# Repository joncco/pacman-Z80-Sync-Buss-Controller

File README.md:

This is a reproduction of the Z80 Sync Buss Controller used in Midway's Pac-Man arcade PCB.

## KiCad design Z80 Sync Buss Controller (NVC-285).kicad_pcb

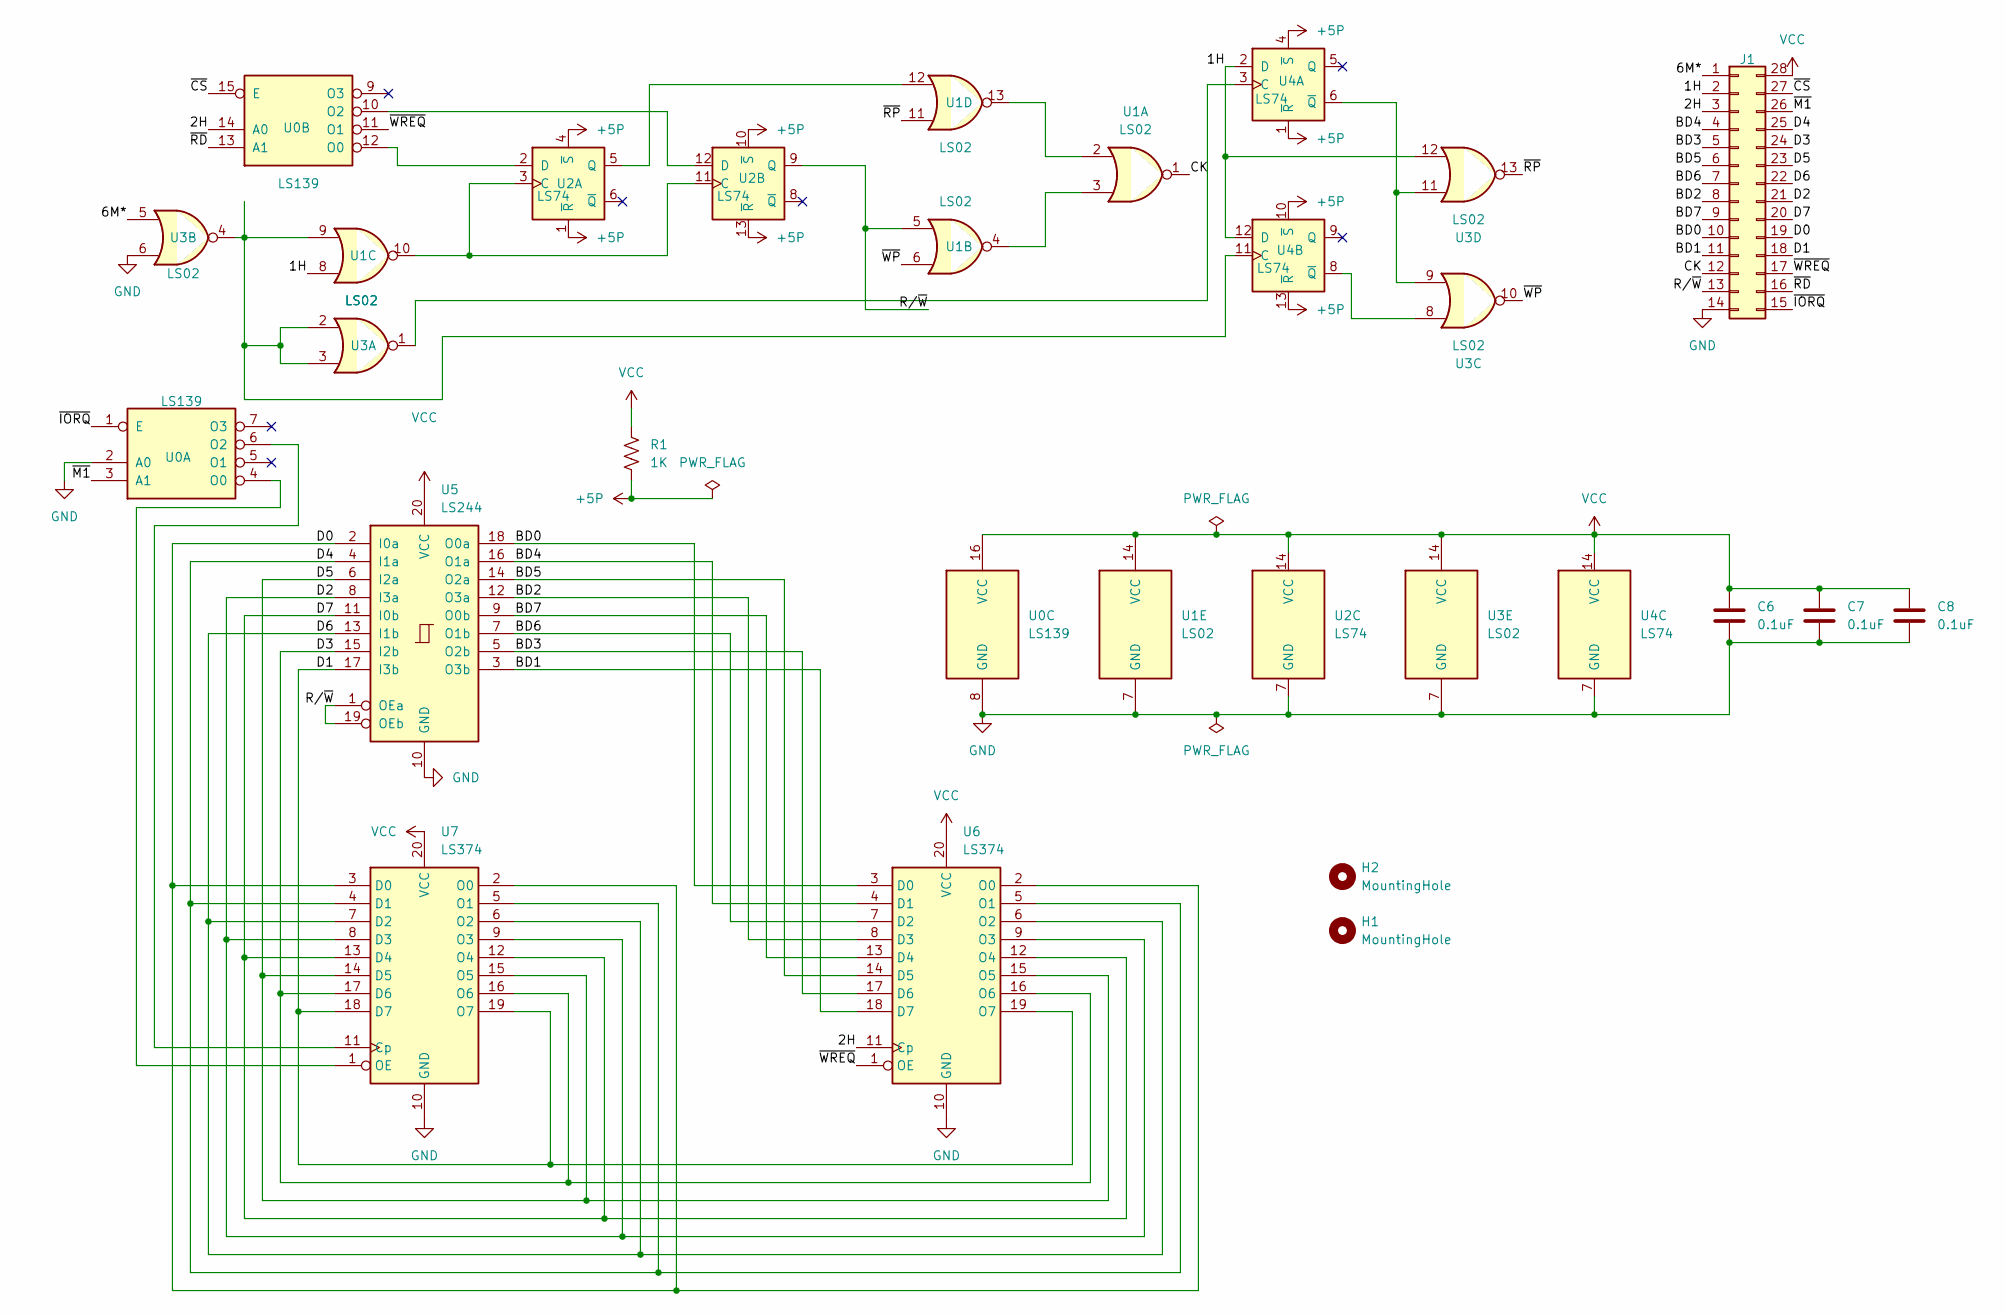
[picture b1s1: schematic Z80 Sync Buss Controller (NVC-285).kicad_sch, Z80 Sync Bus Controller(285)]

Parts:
C6, C7, C8: 0.1uF; C_Axial_L3.8mm_D2.5mm_P12.685mm_Horizontal
H1, H2: MountingHole; MountingHole_3mm
J1: Conn_02x12_Counter_Clockwise; DIP-28_W15.24mm_LongPads
R1: 1K; R_Axial_DIN0207_L6.3mm_D2.5mm_P12.685mm_Horizontal
U0: LS139; DIP-16_W7.62mm_LongPads
U1, U3: LS02; DIP-14_W7.62mm_LongPads
U2, U4: LS74; DIP-14_W7.62mm_LongPads
U5: LS244; DIP-20_W7.62mm_LongPads
U6, U7: LS374; DIP-20_W7.62mm_LongPads

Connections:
+5P: R1.2, U2.1 (~R), U2.4 (~S), U2.10 (~S), U2.13 (~R), U4.1 (~R), U4.4 (~S), U4.10 (~S), U4.13 (~R)
/1H: J1.2, U1.8, U3.12, U4.2 (D), U4.12 (D)
/2H: J1.3, U0.14 (A0), U6.11 (Cp)
/6M*: J1.1, U3.5
/BD0: J1.10, U5.18 (O0a), U6.3 (D0)
/BD1: J1.11, U5.3 (O3b), U6.18 (D7)
/BD2: J1.8, U5.12 (O3a), U6.8 (D3)
/BD3: J1.5, U5.5 (O2b), U6.17 (D6)
/BD4: J1.4, U5.16 (O1a), U6.4 (D1)
/BD5: J1.6, U5.14 (O2a), U6.14 (D5)
/BD6: J1.7, U5.7 (O1b), U6.7 (D2)
/BD7: J1.9, U5.9 (O0b), U6.13 (D4)
/CK: J1.12, U1.1
/D0: J1.19, U5.2 (I0a), U6.2 (O0), U7.2 (O0), U7.3 (D0)
/D1: J1.18, U5.17 (I3b), U6.19 (O7), U7.18 (D7), U7.19 (O7)
/D2: J1.21, U5.8 (I3a), U6.9 (O3), U7.8 (D3), U7.9 (O3)
/D3: J1.24, U5.15 (I2b), U6.16 (O6), U7.16 (O6), U7.17 (D6)
/D4: J1.25, U5.4 (I1a), U6.5 (O1), U7.4 (D1), U7.5 (O1)
/D5: J1.23, U5.6 (I2a), U6.15 (O5), U7.14 (D5), U7.15 (O5)
/D6: J1.22, U5.13 (I1b), U6.6 (O2), U7.6 (O2), U7.7 (D2)
/D7: J1.20, U5.11 (I0b), U6.12 (O4), U7.12 (O4), U7.13 (D4)
/R/~W: J1.13, U1.5, U2.9 (Q), U5.1 (OEa), U5.19 (OEb)
/~CS: J1.27, U0.15 (E)
/~IORQ: J1.15, U0.1 (E)
/~M1: J1.26, U0.3 (A1)
/~RD: J1.16, U0.13 (A1)
/~RP: U1.11, U3.13
/~WP: U1.6, U3.10
/~WREQ: J1.17, U0.11 (O1), U6.1 (OE)
GND: C6.2, C7.2, C8.2, J1.14, U0.2 (A0), U0.8 (GND), U1.7 (GND), U2.7 (GND), U3.6, U3.7 (GND), U4.7 (GND), U5.10 (GND), U6.10 (GND), U7.10 (GND)
unnamed: U0.4 (O0), U7.1 (OE)
unnamed: U0.6 (O2), U7.11 (Cp)
unnamed: U0.12 (O0), U2.2 (D)
unnamed: U0.10 (O2), U2.12 (D)
unnamed: U1.3, U1.4
unnamed: U1.2, U1.13
unnamed: U1.10, U2.3 (C), U2.11 (C)
unnamed: U1.12, U2.5 (Q)
unnamed: U3.1, U4.3 (C)
unnamed: U3.9, U3.11, U4.6 (~Q)
unnamed: U1.9, U3.2, U3.3, U3.4, U4.11 (C)
unnamed: U3.8, U4.8 (~Q)
VCC: C6.1, C7.1, C8.1, J1.28, R1.1, U0.16 (VCC), U1.14 (VCC), U2.14 (VCC), U3.14 (VCC), U4.14 (VCC), U5.20 (VCC), U6.20 (VCC), U7.20 (VCC)

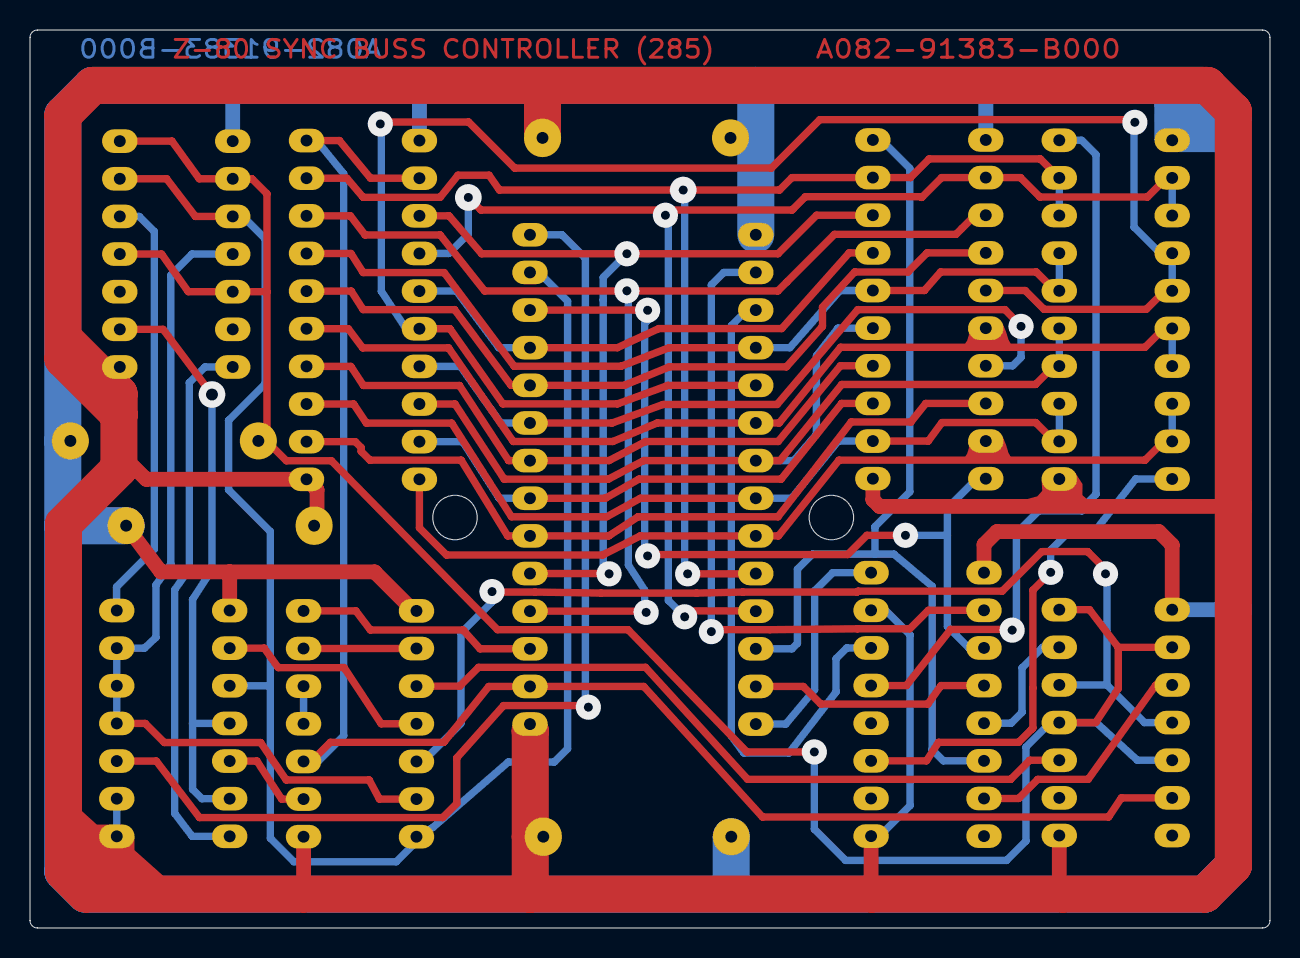
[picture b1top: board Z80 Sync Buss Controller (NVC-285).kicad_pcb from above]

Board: 2 copper layers, 83.7 x 60.6 mm, 15 parts (0 on the bottom side), 43 nets.

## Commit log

2024-12-12 Add CC-BY-4.0 License
2024-12-12 Fix PCB Title
